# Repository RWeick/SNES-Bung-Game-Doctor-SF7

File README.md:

# SNES-Bung-Game-Doctor-SF7
The Kicad files and rom for the Bung Game Doctor SF7 for the SNES

This board has been tested and confirmed.
**30 Sep 2026: Thank you to CoolChecker for discovering that somehow a net failed to be connected - TC was not routed from the ASIC to the Floppy Controller. This has now been corrected.

Mainboard PCB Thickness: 1.6 mm
RAM PCB Thicknesses: 1.2 mm
SNES Attachment PCB Thickness: 1.2 mm

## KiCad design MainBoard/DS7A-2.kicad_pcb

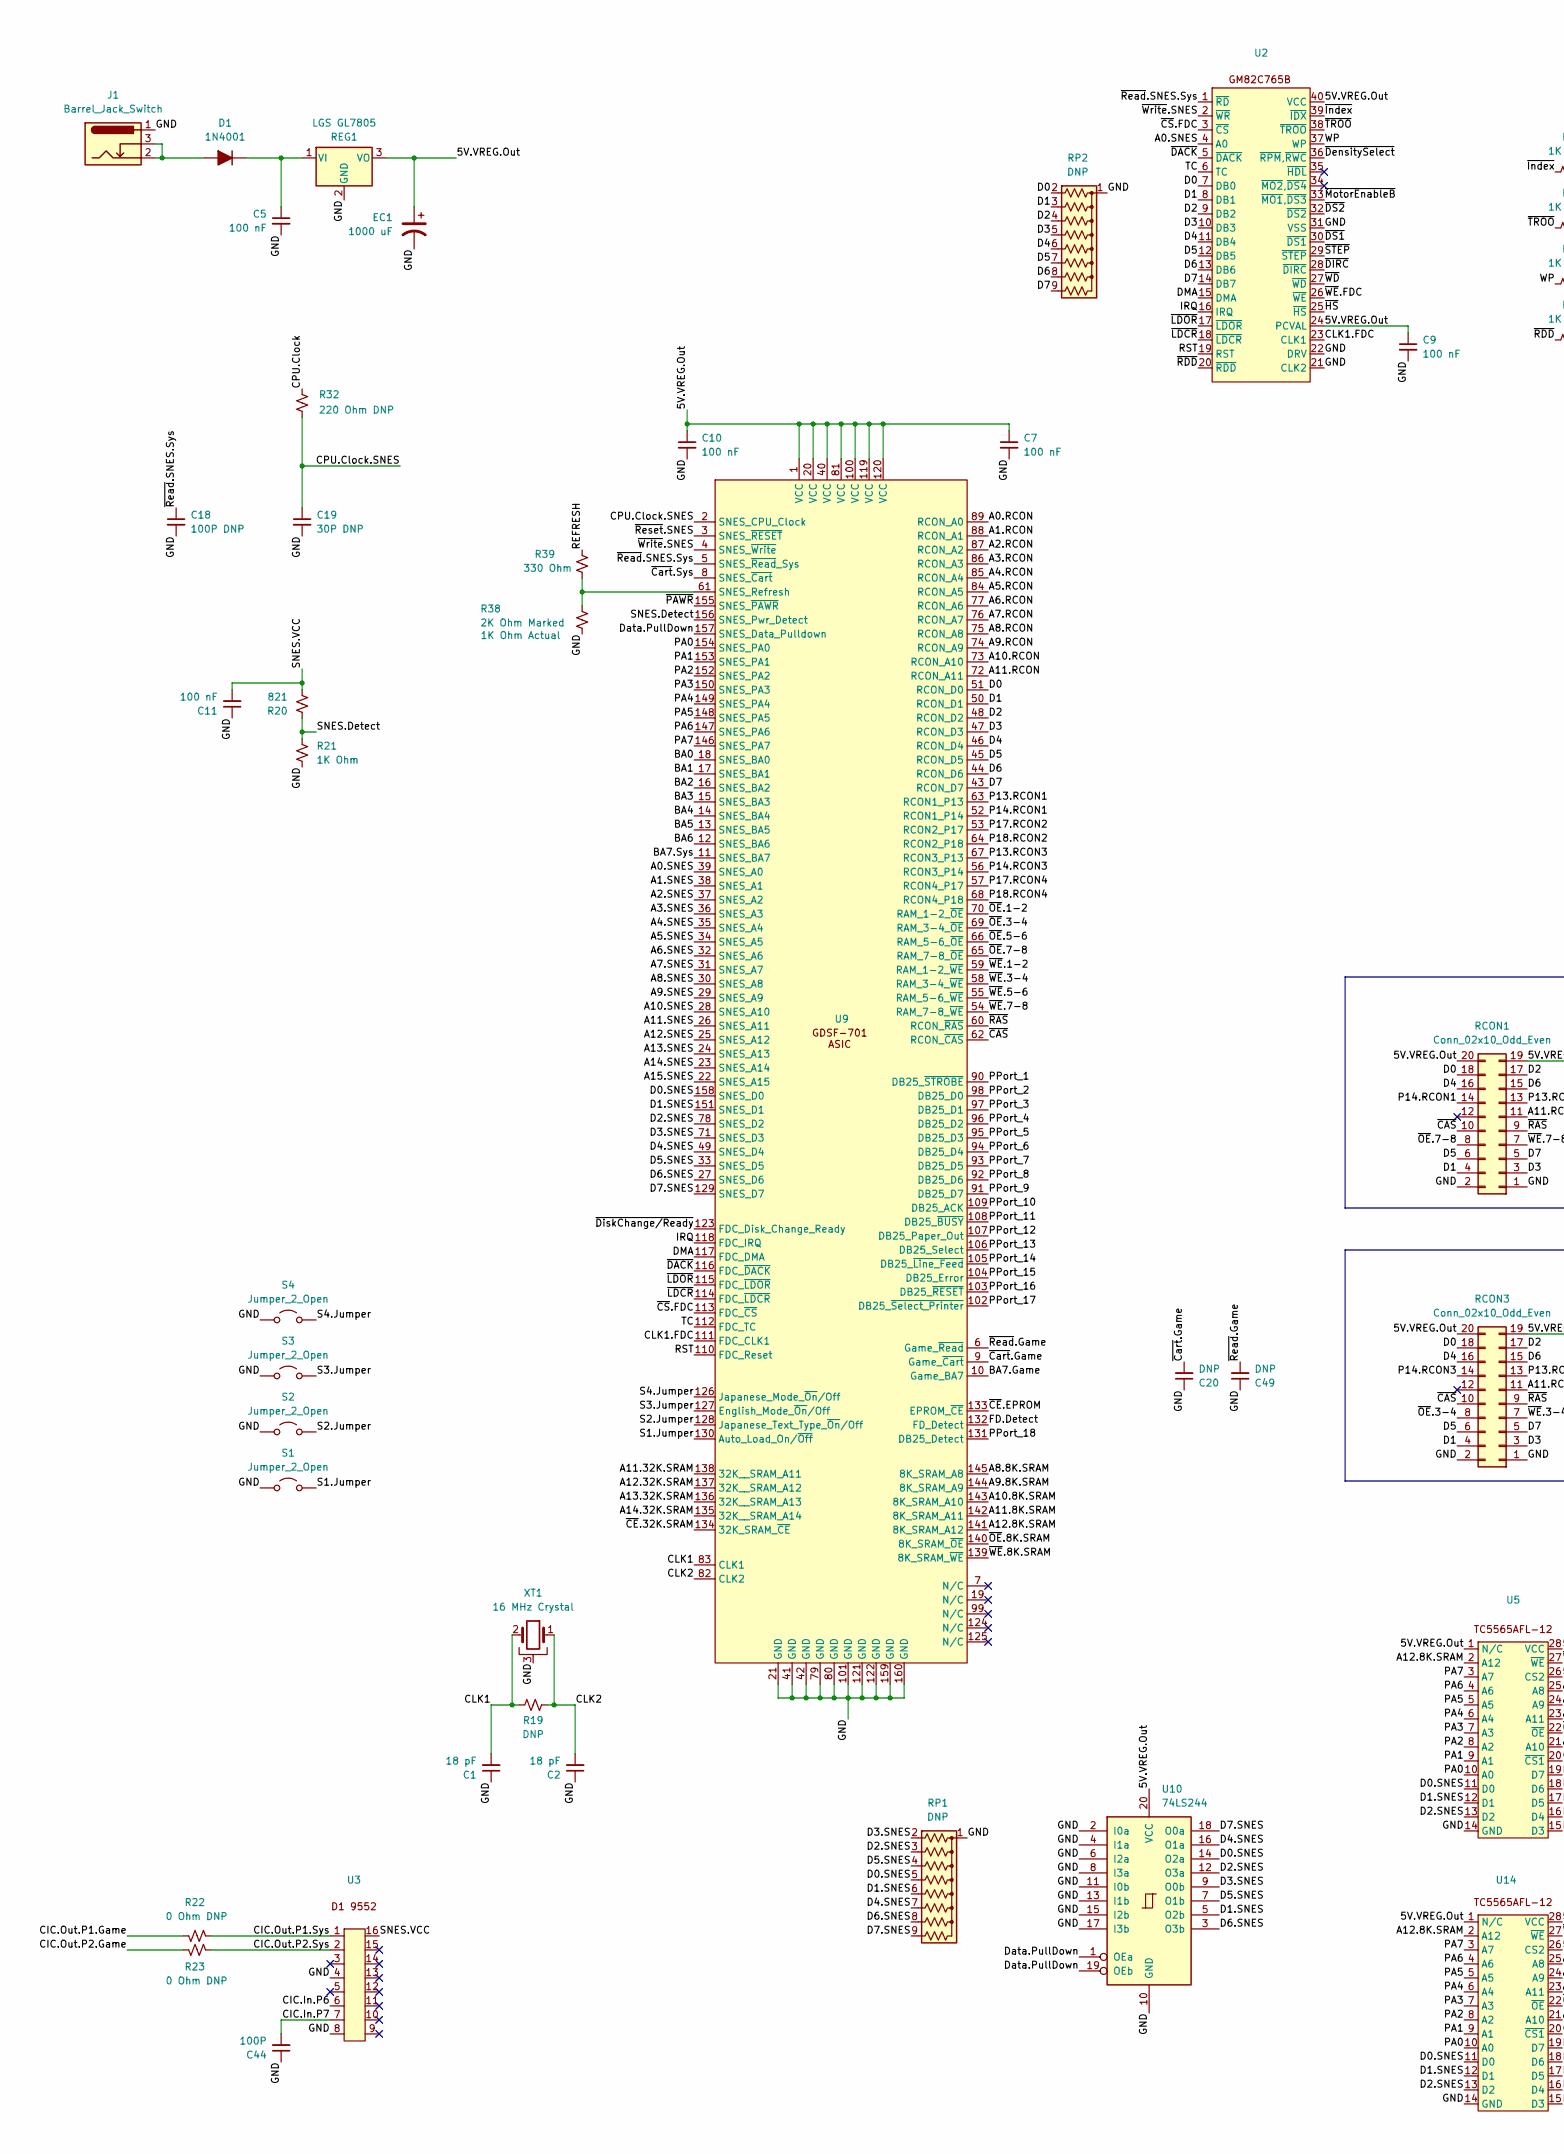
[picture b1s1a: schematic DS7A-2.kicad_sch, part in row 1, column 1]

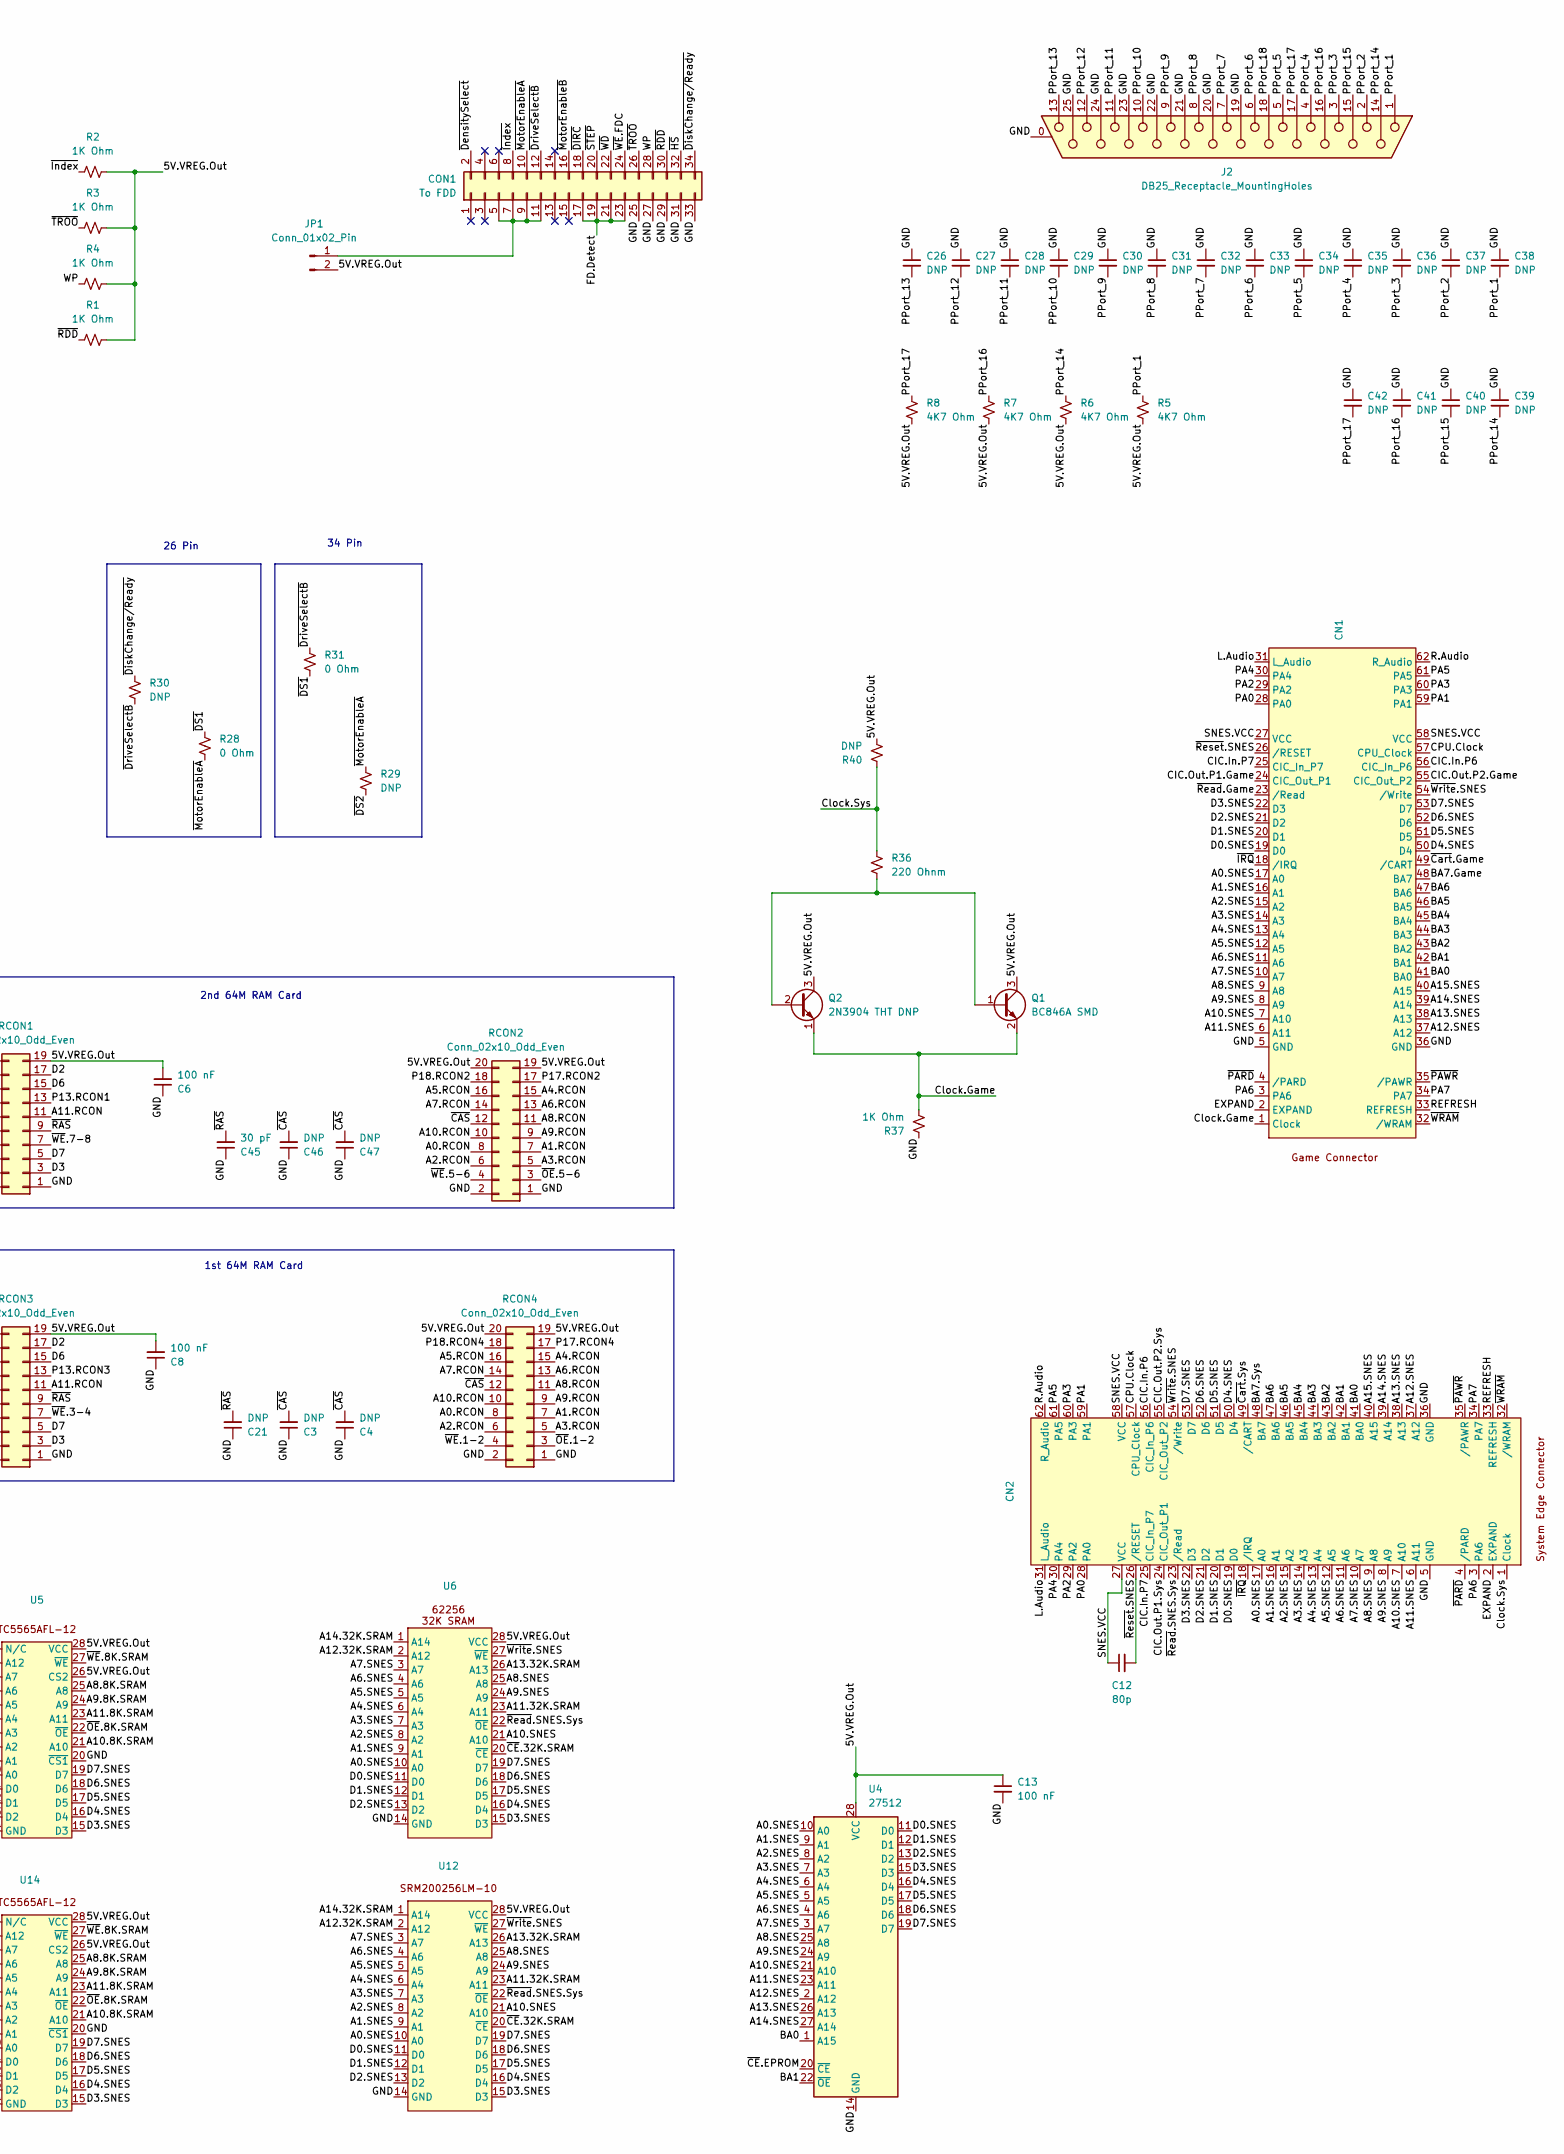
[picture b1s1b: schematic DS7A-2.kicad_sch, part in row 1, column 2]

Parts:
C1, C2: 18 pF; SMD Cap
C3, C4, C20, C21, C26, C27, C28, C29, C30, C31, C32, C33, C34, C35, C36, C37, C38, C39, C40, C41, C42, C46, C47, C49: DNP; SMD Cap
C5, C6, C7, C8, C9, C10, C11, C13: 100 nF; SMD Cap
C12: 80p; SMD Cap
C18: 100P DNP; SMD Cap
C19: 30P DNP; SMD Cap
C44: 100P; SMD Cap
C45: 30 pF; SMD Cap
CN1, CN2: Cartridge Slot
CON1: To FDD; PinSocket_2x17_P2.54mm_Vertical
D1: 1N4001; D_DO-41_SOD81_P10.16mm_Horizontal
EC1: 1000 uF; CP_Radial_D8.0mm_P3.50mm
J1: Barrel_Jack_Switch; DC Jack
J2: DB25_Receptacle_MountingHoles; DSUB-25_Female_Horizontal_P2.77x2.84mm_EdgePinOffset9.90mm_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
JP1: Conn_01x02_Pin; PinHeader_1x02_P2.54mm_Vertical
Q1: BC846A SMD; SOT-23
Q2: 2N3904 THT DNP; TO-92_Inline
R1, R2, R3, R4, R21, R37: 1K Ohm; SMD Resistor
R5, R6, R7, R8: 4K7 Ohm; SMD Resistor
R19, R29, R30, R40: DNP; SMD Resistor
R20: 821; SMD Resistor
R22, R23: 0 Ohm DNP; SMD Resistor
R28, R31: 0 Ohm; SMD Resistor
R32: 220 Ohm DNP; SMD Resistor
R36: 220 Ohnm; SMD Resistor
R38: 2K Ohm Marked; SMD Resistor
R39: 330 Ohm; SMD Resistor
RCON1, RCON2, RCON3, RCON4: Conn_02x10_Odd_Even; PinHeader_2x10_P2.54mm_Vertical
REG1: LGS GL7805; TO-220-3_Vertical
RP1, RP2: DNP; R_Array_SIP9
S1, S2, S3, S4: Jumper_2_Open; SolderJumper-2_P1.3mm_Open_RoundedPad1.0x1.5mm
U2: DIP-40_W15.24mm
U3: DIP-16_W7.62mm
U4: 27512; DIP-28_W15.24mm
U5, U6: DIP-28_W15.24mm
U9: GDSF-701
U10: 74LS244; DIP-20_W7.62mm
U12, U14: SOP-28_8.4x18.16mm_P1.27mm
XT1: 16 MHz Crystal; Crystal_AT310_D3.0mm_L10.0mm_Horizontal_1EP_style1

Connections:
/5V.VREG.Out: C6.2, C7.1, C8.2, C9.1, C10.1, C13.1, EC1.1, JP1.2, Q1.3 (C), Q2.3 (C), R1.2, R2.2, R3.2, R4.2, R5.2, R6.2, R7.2, R8.2, R40.2, RCON1.19, RCON1.20, RCON2.19, RCON2.20, RCON3.19, RCON3.20, RCON4.19, RCON4.20, REG1.3 (VO), U2.24 (PCVAL), U2.40 (VCC), U4.28 (VCC), U5.1 (N/C), U5.26 (CS2), U5.28 (VCC), U6.28 (VCC), U9.1 (VCC), U9.20 (VCC), U9.40 (VCC), U9.81 (VCC), U9.100 (VCC), U9.119 (VCC), U9.120 (VCC), U10.20 (VCC), U12.28 (VCC), U14.1 (N/C), U14.26 (CS2), U14.28 (VCC)
/A0.RCON: RCON2.8, RCON4.8, U9.89 (RCON_A0)
/A0.SNES: CN1.17 (A0), CN2.17 (A0), U2.4 (A0), U4.10 (A0), U6.10 (A0), U9.39 (SNES_A0), U12.10 (A0)
/A1.RCON: RCON2.7, RCON4.7, U9.88 (RCON_A1)
/A1.SNES: CN1.16 (A1), CN2.16 (A1), U4.9 (A1), U6.9 (A1), U9.38 (SNES_A1), U12.9 (A1)
/A2.RCON: RCON2.6, RCON4.6, U9.87 (RCON_A2)
/A2.SNES: CN1.15 (A2), CN2.15 (A2), U4.8 (A2), U6.8 (A2), U9.37 (SNES_A2), U12.8 (A2)
/A3.RCON: RCON2.5, RCON4.5, U9.86 (RCON_A3)
/A3.SNES: CN1.14 (A3), CN2.14 (A3), U4.7 (A3), U6.7 (A3), U9.36 (SNES_A3), U12.7 (A3)
/A4.RCON: RCON2.15, RCON4.15, U9.85 (RCON_A4)
/A4.SNES: CN1.13 (A4), CN2.13 (A4), U4.6 (A4), U6.6 (A4), U9.35 (SNES_A4), U12.6 (A4)
/A5.RCON: RCON2.16, RCON4.16, U9.84 (RCON_A5)
/A5.SNES: CN1.12 (A5), CN2.12 (A5), U4.5 (A5), U6.5 (A5), U9.34 (SNES_A5), U12.5 (A5)
/A6.RCON: RCON2.13, RCON4.13, U9.77 (RCON_A6)
/A6.SNES: CN1.11 (A6), CN2.11 (A6), U4.4 (A6), U6.4 (A6), U9.32 (SNES_A6), U12.4 (A6)
/A7.RCON: RCON2.14, RCON4.14, U9.76 (RCON_A7)
/A7.SNES: CN1.10 (A7), CN2.10 (A7), U4.3 (A7), U6.3 (A7), U9.31 (SNES_A7), U12.3 (A7)
/A8.8K.SRAM: U5.25 (A8), U9.145 (8K_SRAM_A8), U14.25 (A8)
/A8.RCON: RCON2.11, RCON4.11, U9.75 (RCON_A8)
/A8.SNES: CN1.9 (A8), CN2.9 (A8), U4.25 (A8), U6.25 (A8), U9.30 (SNES_A8), U12.25 (A8)
/A9.8K.SRAM: U5.24 (A9), U9.144 (8K_SRAM_A9), U14.24 (A9)
/A9.RCON: RCON2.9, RCON4.9, U9.74 (RCON_A9)
/A9.SNES: CN1.8 (A9), CN2.8 (A9), U4.24 (A9), U6.24 (A9), U9.29 (SNES_A9), U12.24 (A9)
/A10.8K.SRAM: U5.21 (A10), U9.143 (8K_SRAM_A10), U14.21 (A10)
/A10.RCON: RCON2.10, RCON4.10, U9.73 (RCON_A10)
/A10.SNES: CN1.7 (A10), CN2.7 (A10), U4.21 (A10), U6.21 (A10), U9.28 (SNES_A10), U12.21 (A10)
/A11.8K.SRAM: U5.23 (A11), U9.142 (8K_SRAM_A11), U14.23 (A11)
/A11.32K.SRAM: U6.23 (A11), U9.138 (32K__SRAM_A11), U12.23 (A11)
/A11.RCON: RCON1.11, RCON3.11, U9.72 (RCON_A11)
/A11.SNES: CN1.6 (A11), CN2.6 (A11), U4.23 (A11), U9.26 (SNES_A11)
/A12.8K.SRAM: U5.2 (A12), U9.141 (8K_SRAM_A12), U14.2 (A12)
/A12.32K.SRAM: U6.2 (A12), U9.137 (32K__SRAM_A12), U12.2 (A12)
/A12.SNES: CN1.37 (A12), CN2.37 (A12), U4.2 (A12), U9.25 (SNES_A12)
/A13.32K.SRAM: U6.26 (A13), U9.136 (32K__SRAM_A13), U12.26 (A13)
/A13.SNES: CN1.38 (A13), CN2.38 (A13), U4.26 (A13), U9.24 (SNES_A13)
/A14.32K.SRAM: U6.1 (A14), U9.135 (32K__SRAM_A14), U12.1 (A14)
/A14.SNES: CN1.39 (A14), CN2.39 (A14), U4.27 (A14), U9.23 (SNES_A14)
/A15.SNES: CN1.40 (A15), CN2.40 (A15), U9.22 (SNES_A15)
/BA0: CN1.41 (BA0), CN2.41 (BA0), U4.1 (A15), U9.18 (SNES_BA0)
/BA1: CN1.42 (BA1), CN2.42 (BA1), U4.22 (~OE), U9.17 (SNES_BA1)
/BA2: CN1.43 (BA2), CN2.43 (BA2), U9.16 (SNES_BA2)
/BA3: CN1.44 (BA3), CN2.44 (BA3), U9.15 (SNES_BA3)
/BA4: CN1.45 (BA4), CN2.45 (BA4), U9.14 (SNES_BA4)
/BA5: CN1.46 (BA5), CN2.46 (BA5), U9.13 (SNES_BA5)
/BA6: CN1.47 (BA6), CN2.47 (BA6), U9.12 (SNES_BA6)
/BA7.Game: CN1.48 (BA7), U9.10 (Game_BA7)
/BA7.Sys: CN2.48 (BA7), U9.11 (SNES_BA7)
/CIC.In.P6: CN1.56 (CIC_In_P6), CN2.56 (CIC_In_P6), U3.6
/CIC.In.P7: C44.2, CN1.25 (CIC_In_P7), CN2.25 (CIC_In_P7), U3.7
/CIC.Out.P1.Game: CN1.24 (CIC_Out_P1), R22.1
/CIC.Out.P1.Sys: CN2.24 (CIC_Out_P1), R22.2, U3.1
/CIC.Out.P2.Game: CN1.55 (CIC_Out_P2), R23.1
/CIC.Out.P2.Sys: CN2.55 (CIC_Out_P2), R23.2, U3.2
/CLK1: C1.2, R19.1, U9.83 (CLK1), XT1.2
/CLK1.FDC: U2.23 (CLK1), U9.111 (FDC_CLK1)
/CLK2: C2.2, R19.2, U9.82 (CLK2), XT1.1
/CPU.Clock: CN1.57 (CPU_Clock), CN2.57 (CPU_Clock), R32.2
/CPU.Clock.SNES: C19.1, R32.1, U9.2 (SNES_CPU_Clock)
/Clock.Game: CN1.1 (Clock), Q1.2 (E), Q2.1 (E), R37.2
/Clock.Sys: CN2.1 (Clock), R36.1, R40.1
/D0: RCON1.18, RCON3.18, RP2.2 (R1), U2.7 (DB0), U9.51 (RCON_D0)
/D0.SNES: CN1.19 (D0), CN2.19 (D0), RP1.5 (R4), U4.11 (D0), U5.11 (D0), U6.11 (D0), U9.158 (SNES_D0), U10.14 (O2a), U12.11 (D0), U14.11 (D0)
/D1: RCON1.4, RCON3.4, RP2.3 (R2), U2.8 (DB1), U9.50 (RCON_D1)
/D1.SNES: CN1.20 (D1), CN2.20 (D1), RP1.6 (R5), U4.12 (D1), U5.12 (D1), U6.12 (D1), U9.151 (SNES_D1), U10.5 (O2b), U12.12 (D1), U14.12 (D1)
/D2: RCON1.17, RCON3.17, RP2.4 (R3), U2.9 (DB2), U9.48 (RCON_D2)
/D2.SNES: CN1.21 (D2), CN2.21 (D2), RP1.3 (R2), U4.13 (D2), U5.13 (D2), U6.13 (D2), U9.78 (SNES_D2), U10.12 (O3a), U12.13 (D2), U14.13 (D2)
/D3: RCON1.3, RCON3.3, RP2.5 (R4), U2.10 (DB3), U9.47 (RCON_D3)
/D3.SNES: CN1.22 (D3), CN2.22 (D3), RP1.2 (R1), U4.15 (D3), U5.15 (D3), U6.15 (D3), U9.71 (SNES_D3), U10.9 (O0b), U12.15 (D3), U14.15 (D3)
/D4: RCON1.16, RCON3.16, RP2.6 (R5), U2.11 (DB4), U9.46 (RCON_D4)
/D4.SNES: CN1.50 (D4), CN2.50 (D4), RP1.7 (R6), U4.16 (D4), U5.16 (D4), U6.16 (D4), U9.49 (SNES_D4), U10.16 (O1a), U12.16 (D4), U14.16 (D4)
/D5: RCON1.6, RCON3.6, RP2.7 (R6), U2.12 (DB5), U9.45 (RCON_D5)
/D5.SNES: CN1.51 (D5), CN2.51 (D5), RP1.4 (R3), U4.17 (D5), U5.17 (D5), U6.17 (D5), U9.33 (SNES_D5), U10.7 (O1b), U12.17 (D5), U14.17 (D5)
/D6: RCON1.15, RCON3.15, RP2.8 (R7), U2.13 (DB6), U9.44 (RCON_D6)
/D6.SNES: CN1.52 (D6), CN2.52 (D6), RP1.8 (R7), U4.18 (D6), U5.18 (D6), U6.18 (D6), U9.27 (SNES_D6), U10.3 (O3b), U12.18 (D6), U14.18 (D6)
/D7: RCON1.5, RCON3.5, RP2.9 (R8), U2.14 (DB7), U9.43 (RCON_D7)
/D7.SNES: CN1.53 (D7), CN2.53 (D7), RP1.9 (R8), U4.19 (D7), U5.19 (D7), U6.19 (D7), U9.129 (SNES_D7), U10.18 (O0a), U12.19 (D7), U14.19 (D7)
/DMA: U2.15 (DMA), U9.117 (FDC_DMA)
/Data.PullDown: U9.157 (SNES_Data_Pulldown), U10.1 (OEa), U10.19 (OEb)
/EXPAND: CN1.2 (EXPAND), CN2.2 (EXPAND)
/FD.Detect: CON1.17, CON1.19, CON1.21, CON1.23, U9.132 (FD_Detect)
/GND: C1.1, C2.1, C3.1, C4.1, C5.2, C6.1, C7.2, C8.1, C9.2, C10.2, C11.1, C13.2, C18.2, C19.2, C20.1, C21.1, C26.1, C27.1, C28.1, C29.1, C30.1, C31.1, C32.1, C33.1, C34.1, C35.1, C36.1, C37.1, C38.1, C39.1, C40.1, C41.1, C42.1, C44.1, C45.1, C46.1, C47.1, C49.1, CN1.5 (GND), CN1.36 (GND), CN2.5 (GND), CN2.36 (GND), CON1.25, CON1.27, CON1.29, CON1.31, CON1.33, EC1.2, J1.1, J2.0 (PAD), J2.19, J2.20, J2.21, J2.22, J2.23, J2.24, J2.25, R21.2, R37.1, R38.1, RCON1.1, RCON1.2, RCON2.1, RCON2.2, RCON3.1, RCON3.2, RCON4.1, RCON4.2, REG1.2 (GND), RP1.1 (common), RP2.1 (common), S1.1 (A), S2.1 (A), S3.1 (A), S4.1 (A), U2.21 (CLK2), U2.22 (DRV), U2.31 (VSS), U3.4, U3.8, U4.14 (GND), U5.14 (GND), U5.20 (~CS1), U6.14 (GND), U9.21 (GND), U9.41 (GND), U9.42 (GND), U9.79 (GND), U9.80 (GND), U9.101 (GND), U9.121 (GND), U9.122 (GND), U9.159 (GND), U9.160 (GND), U10.2 (I0a), U10.4 (I1a), U10.6 (I2a), U10.8 (I3a), U10.10 (GND), U10.11 (I0b), U10.13 (I1b), U10.15 (I2b), U10.17 (I3b), U12.14 (GND), U14.14 (GND), U14.20 (~CS1), XT1.3
/IRQ: U2.16 (IRQ), U9.118 (FDC_IRQ)
/L.Audio: CN1.31 (L_Audio), CN2.31 (L_Audio)
/P13.RCON1: RCON1.13, U9.63 (RCON1_P13)
/P13.RCON3: RCON3.13, U9.67 (RCON3_P13)
/P14.RCON1: RCON1.14, U9.52 (RCON1_P14)
/P14.RCON3: RCON3.14, U9.56 (RCON3_P14)
/P17.RCON2: RCON2.17, U9.53 (RCON2_P17)
/P17.RCON4: RCON4.17, U9.57 (RCON4_P17)
/P18.RCON2: RCON2.18, U9.64 (RCON2_P18)
/P18.RCON4: RCON4.18, U9.68 (RCON4_P18)
/PA0: CN1.28 (PA0), CN2.28 (PA0), U5.10 (A0), U9.154 (SNES_PA0), U14.10 (A0)
/PA1: CN1.59 (PA1), CN2.59 (PA1), U5.9 (A1), U9.153 (SNES_PA1), U14.9 (A1)
/PA2: CN1.29 (PA2), CN2.29 (PA2), U5.8 (A2), U9.152 (SNES_PA2), U14.8 (A2)
/PA3: CN1.60 (PA3), CN2.60 (PA3), U5.7 (A3), U9.150 (SNES_PA3), U14.7 (A3)
/PA4: CN1.30 (PA4), CN2.30 (PA4), U5.6 (A4), U9.149 (SNES_PA4), U14.6 (A4)
/PA5: CN1.61 (PA5), CN2.61 (PA5), U5.5 (A5), U9.148 (SNES_PA5), U14.5 (A5)
/PA6: CN1.3 (PA6), CN2.3 (PA6), U5.4 (A6), U9.147 (SNES_PA6), U14.4 (A6)
/PA7: CN1.34 (PA7), CN2.34 (PA7), U5.3 (A7), U9.146 (SNES_PA7), U14.3 (A7)
/PPort_1: C38.2, J2.1, R5.1, U9.90 (DB25_~STROBE)
/PPort_2: C37.2, J2.2, U9.98 (DB25_D0)
/PPort_3: C36.2, J2.3, U9.97 (DB25_D1)
/PPort_4: C35.2, J2.4, U9.96 (DB25_D2)
/PPort_5: C34.2, J2.5, U9.95 (DB25_D3)
/PPort_6: C33.2, J2.6, U9.94 (DB25_D4)
/PPort_7: C32.2, J2.7, U9.93 (DB25_D5)
/PPort_8: C31.2, J2.8, U9.92 (DB25_D6)
/PPort_9: C30.2, J2.9, U9.91 (DB25_D7)
/PPort_10: C29.2, J2.10, U9.109 (DB25_ACK)
/PPort_11: C28.2, J2.11, U9.108 (DB25_~BUSY)
/PPort_12: C27.2, J2.12, U9.107 (DB25_Paper_Out)
/PPort_13: C26.2, J2.13, U9.106 (DB25_Select)
/PPort_14: C39.2, J2.14, R6.1, U9.105 (DB25_~Line_Feed)
/PPort_15: C40.2, J2.15, U9.104 (DB25_Error)
/PPort_16: C41.2, J2.16, R7.1, U9.103 (DB25_~RESET)
/PPort_17: C42.2, J2.17, R8.1, U9.102 (DB25_~Select_Printer)
/PPort_18: J2.18, U9.131 (DB25_Detect)
/R.Audio: CN1.62 (R_Audio), CN2.62 (R_Audio)
/REFRESH: CN1.33 (REFRESH), CN2.33 (REFRESH), R39.2
/RST: U2.19 (RST), U9.110 (FDC_Reset)
/S1.Jumper: S1.2 (B), U9.130 (Auto_Load_On/~Off)
/S2.Jumper: S2.2 (B), U9.128 (Japanese_Text_Type_~On/Off)
/S3.Jumper: S3.2 (B), U9.127 (English_Mode_~On/Off)
/S4.Jumper: S4.2 (B), U9.126 (Japanese_Mode_~On/Off)
/SNES.Detect: R20.1, R21.1, U9.156 (SNES_Pwr_Detect)
/SNES.VCC: C11.2, C12.1, CN1.27 (VCC), CN1.58 (VCC), CN2.27 (VCC), CN2.58 (VCC), R20.2, U3.16
/TC: U2.6 (TC), U9.112 (FDC_TC)
/WP: CON1.28, R4.1, U2.37 (WP)
/~CAS: C3.2, C4.2, C46.2, C47.2, RCON1.10, RCON2.12, RCON3.10, RCON4.12, U9.62 (RCON_~CAS)
/~CE.32K.SRAM: U6.20 (~CE), U9.134 (32K_SRAM_~CE), U12.20 (~CE)
/~CE.EPROM: U4.20 (~CE), U9.133 (EPROM_~CE)
/~CS.FDC: U2.3 (~CS), U9.113 (FDC_~CS)
/~Cart.Game: C20.2, CN1.49 (/CART), U9.9 (Game_~Cart)
/~Cart.Sys: CN2.49 (/CART), U9.8 (SNES_~Cart)
/~DACK: U2.5 (~DACK), U9.116 (FDC_~DACK)
/~DIRC: CON1.18, U2.28 (~DIRC)
/~DS1: R28.1, R31.2, U2.30 (~DS1)
/~DS2: R29.2, U2.32 (~DS2)
/~DensitySelect: CON1.2, U2.36 (~RPM,~RWC)
/~DiskChange/Ready: CON1.34, R30.1, U9.123 (FDC_Disk_Change_Ready)
/~DriveSelectB: CON1.12, R30.2, R31.1
/~HS: CON1.32, U2.25 (~HS)
/~IRQ: CN1.18 (/IRQ), CN2.18 (/IRQ)
/~Index: CON1.8, R2.1, U2.39 (~IDX)
/~LDCR: U2.18 (~LDCR), U9.114 (FDC_~LDCR)
/~LDOR: U2.17 (~LDOR), U9.115 (FDC_~LDOR)
/~MotorEnableA: CON1.10, R28.2, R29.1
/~MotorEnableB: CON1.16, U2.33 (~MO1,~DS3)
/~OE.1-2: RCON4.3, U9.70 (RAM_1-2_~OE)
/~OE.3-4: RCON3.8, U9.69 (RAM_3-4_~OE)
/~OE.5-6: RCON2.3, U9.66 (RAM_5-6_~OE)
/~OE.7-8: RCON1.8, U9.65 (RAM_7-8_~OE)
/~OE.8K.SRAM: U5.22 (~OE), U9.140 (8K_SRAM_~OE), U14.22 (~OE)
/~PARD: CN1.4 (/PARD), CN2.4 (/PARD)
/~PAWR: CN1.35 (/PAWR), CN2.35 (/PAWR), U9.155 (SNES_~PAWR)
/~RAS: C21.2, C45.2, RCON1.9, RCON3.9, U9.60 (RCON_~RAS)
/~RDD: CON1.30, R1.1, U2.20 (~RDD)
/~Read.Game: C49.2, CN1.23 (/Read), U9.6 (Game_~Read)
/~Read.SNES.Sys: C18.1, CN2.23 (/Read), U2.1 (~RD), U6.22 (~OE), U9.5 (SNES_~Read_Sys), U12.22 (~OE)
/~Reset.SNES: C12.2, CN1.26 (/RESET), CN2.26 (/RESET), U9.3 (SNES_~RESET)
/~STEP: CON1.20, U2.29 (~STEP)
/~TROO: CON1.26, R3.1, U2.38 (~TROO)
/~WD: CON1.22, U2.27 (~WD)
/~WE.1-2: RCON4.4, U9.59 (RAM_1-2_~WE)
/~WE.3-4: RCON3.7, U9.58 (RAM_3-4_~WE)
/~WE.5-6: RCON2.4, U9.55 (RAM_5-6_~WE)
/~WE.7-8: RCON1.7, U9.54 (RAM_7-8_~WE)
/~WE.8K.SRAM: U5.27 (~WE), U9.139 (8K_SRAM_~WE), U14.27 (~WE)
/~WE.FDC: CON1.24, U2.26 (~WE)
/~WRAM: CN1.32 (/WRAM), CN2.32 (/WRAM)
/~Write.SNES: CN1.54 (/Write), CN2.54 (/Write), U2.2 (~WR), U6.27 (~WE), U9.4 (SNES_~Write), U12.27 (~WE)
unnamed: CON1.5, CON1.7, CON1.9, CON1.11, JP1.1
unnamed: D1.2 (A), J1.2, J1.3
unnamed: C5.1, D1.1 (K), REG1.1 (VI)
unnamed: Q1.1 (B), Q2.2 (B), R36.2
unnamed: R38.2, R39.1, U9.61 (SNES_Refresh)

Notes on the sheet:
34 Pin
1st 64M RAM Card
2nd 64M RAM Card
26 Pin

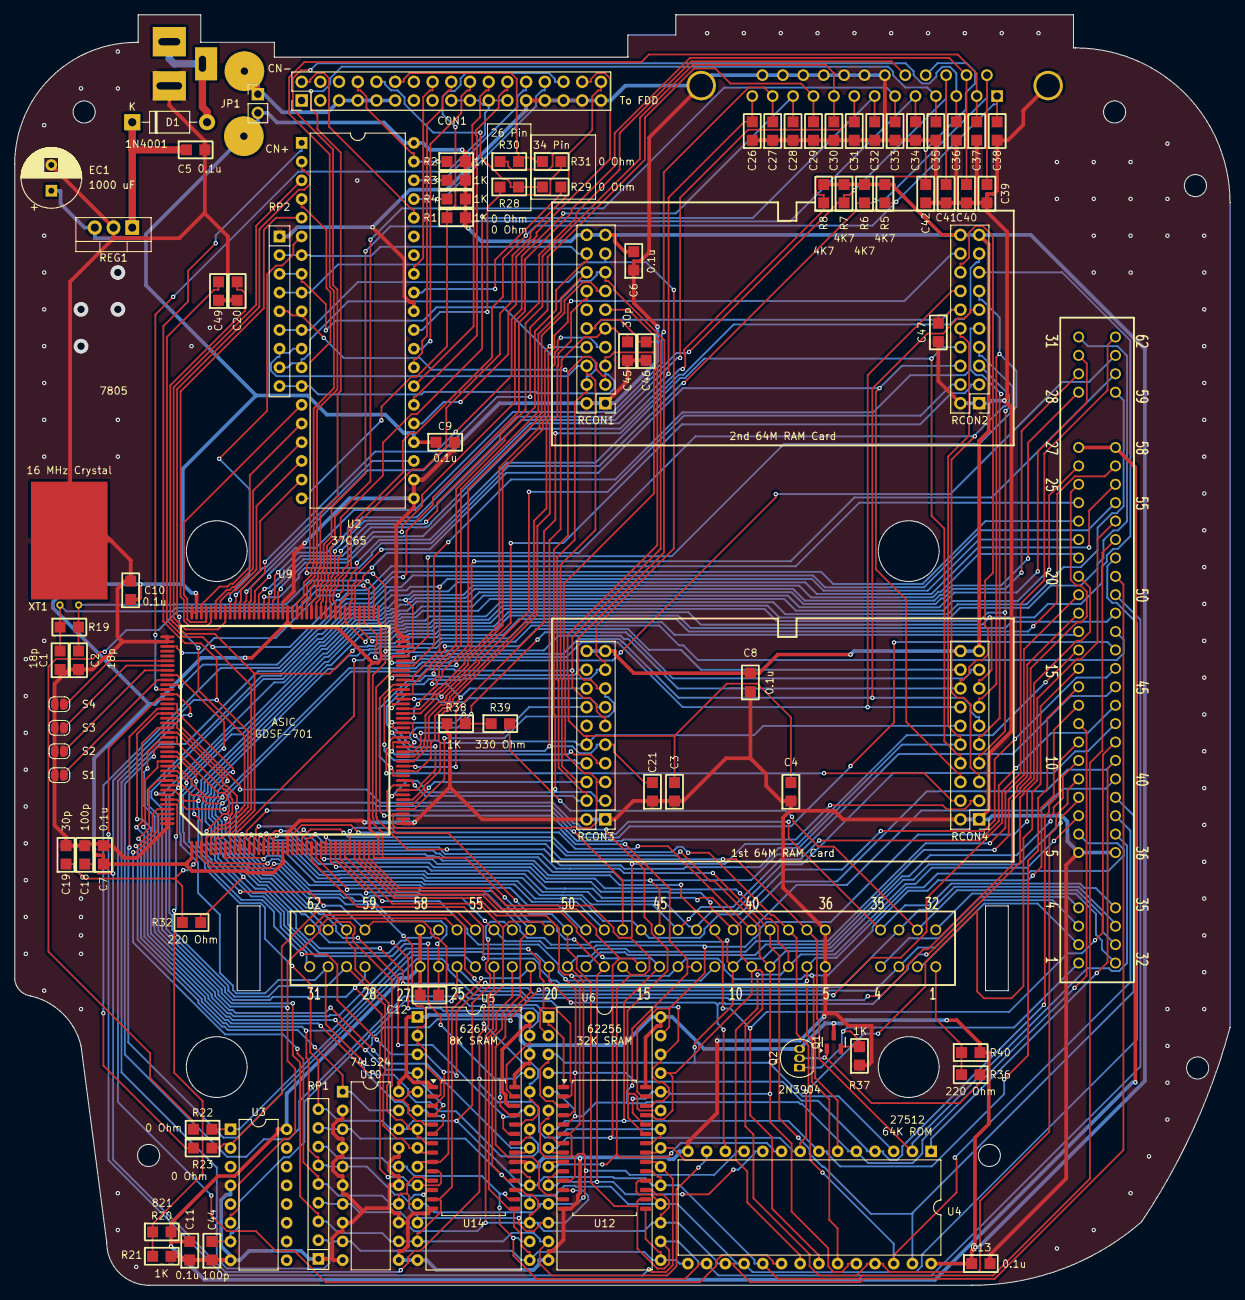
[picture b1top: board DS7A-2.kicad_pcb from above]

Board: 2 copper layers, 165.0 x 172.5 mm, 93 parts (1 on the bottom side), 176 nets.

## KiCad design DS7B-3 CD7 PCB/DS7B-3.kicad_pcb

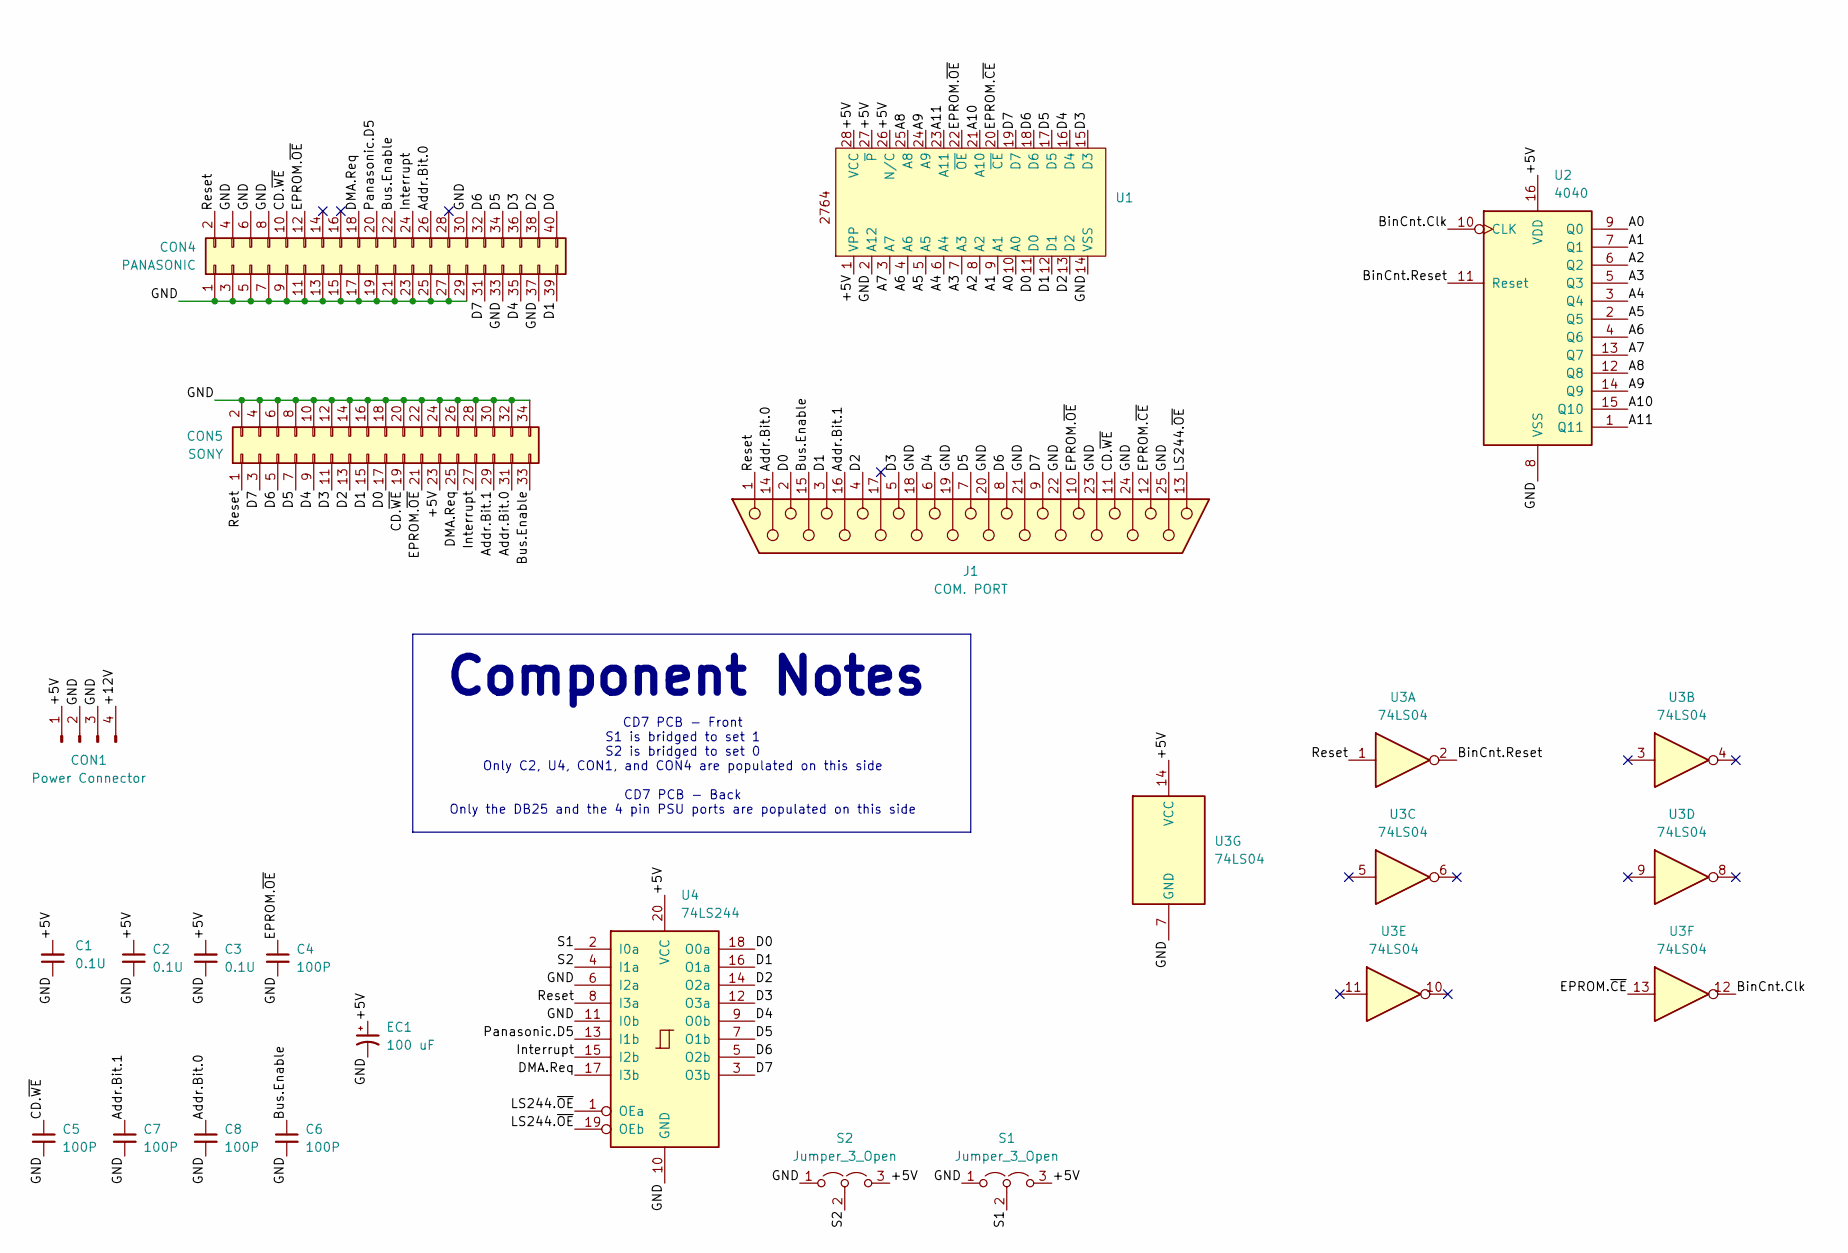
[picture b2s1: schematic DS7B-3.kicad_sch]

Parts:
C1, C2, C3: 0.1U; C_Disc_D5.0mm_W2.5mm_P5.00mm
C4, C5, C6, C7, C8: 100P; C_Disc_D3.8mm_W2.6mm_P2.50mm
CON1: Power Connector; Molex_KK-396_A-41791-0004_1x04_P3.96mm_Vertical
CON4: PANASONIC; IDC-Header_2x20_P2.54mm_Vertical
CON5: SONY; IDC-Header_2x17_P2.54mm_Vertical
EC1: 100 uF; CP_Radial_D8.0mm_P2.50mm
J1: COM. PORT; DSUB-25_Female_Vertical_P2.77x2.84mm_MountingHoles
S1, S2: Jumper_3_Open; PinHeader_1x03_P2.54mm_Vertical
U1: DIP-28_W15.24mm
U2: 4040; DIP-16_W7.62mm
U3: 74LS04; DIP-14_W7.62mm
U4: 74LS244; DIP-20_W7.62mm

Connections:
/+5V: C1.2, C2.1, C3.2, CON1.1, CON5.23, EC1.1, S1.3 (B), S2.3 (B), U1.1 (VPP), U1.26 (N/C), U1.27 (~P), U1.28 (VCC), U2.16 (VDD), U3.14 (VCC), U4.20 (VCC)
/+12V: CON1.4
/A0: U1.10 (A0), U2.9 (Q0)
/A1: U1.9 (A1), U2.7 (Q1)
/A2: U1.8 (A2), U2.6 (Q2)
/A3: U1.7 (A3), U2.5 (Q3)
/A4: U1.6 (A4), U2.3 (Q4)
/A5: U1.5 (A5), U2.2 (Q5)
/A6: U1.4 (A6), U2.4 (Q6)
/A7: U1.3 (A7), U2.13 (Q7)
/A8: U1.25 (A8), U2.12 (Q8)
/A9: U1.24 (A9), U2.14 (Q9)
/A10: U1.21 (A10), U2.15 (Q10)
/A11: U1.23 (A11), U2.1 (Q11)
/Addr.Bit.0: C8.1, CON4.26, CON5.31, J1.14
/Addr.Bit.1: C7.1, CON5.29, J1.16
/BinCnt.Clk: U2.10 (CLK), U3.12
/BinCnt.Reset: U2.11 (Reset), U3.2
/Bus.Enable: C6.1, CON4.22, CON5.33, J1.15
/CD.~WE: C5.1, CON4.10, CON5.19, J1.11
/D0: CON4.40, CON5.17, J1.2, U1.11 (D0), U4.18 (O0a)
/D1: CON4.39, CON5.15, J1.3, U1.12 (D1), U4.16 (O1a)
/D2: CON4.38, CON5.13, J1.4, U1.13 (D2), U4.14 (O2a)
/D3: CON4.36, CON5.11, J1.5, U1.15 (D3), U4.12 (O3a)
/D4: CON4.35, CON5.9, J1.6, U1.16 (D4), U4.9 (O0b)
/D5: CON4.34, CON5.7, J1.7, U1.17 (D5), U4.7 (O1b)
/D6: CON4.32, CON5.5, J1.8, U1.18 (D6), U4.5 (O2b)
/D7: CON4.31, CON5.3, J1.9, U1.19 (D7), U4.3 (O3b)
/DMA.Req: CON4.18, CON5.25, U4.17 (I3b)
/EPROM.~CE: J1.12, U1.20 (~CE), U3.13
/EPROM.~OE: C4.1, CON4.12, CON5.21, J1.10, U1.22 (~OE)
/GND: C1.1, C2.2, C3.1, C4.2, C5.2, C6.2, C7.2, C8.2, CON1.2, CON1.3, CON4.1, CON4.3, CON4.4, CON4.5, CON4.6, CON4.7, CON4.8, CON4.9, CON4.11, CON4.13, CON4.15, CON4.17, CON4.19, CON4.21, CON4.23, CON4.25, CON4.27, CON4.29, CON4.30, CON4.33, CON4.37, CON5.2, CON5.4, CON5.6, CON5.8, CON5.10, CON5.12, CON5.14, CON5.16, CON5.18, CON5.20, CON5.22, CON5.24, CON5.26, CON5.28, CON5.30, CON5.32, CON5.34, EC1.2, J1.18, J1.19, J1.20, J1.21, J1.22, J1.23, J1.24, J1.25, S1.1 (A), S2.1 (A), U1.2 (A12), U1.14 (VSS), U2.8 (VSS), U3.7 (GND), U4.6 (I2a), U4.10 (GND), U4.11 (I0b)
/Interrupt: CON4.24, CON5.27, U4.15 (I2b)
/LS244.~OE: J1.13, U4.1 (OEa), U4.19 (OEb)
/Panasonic.D5: CON4.20, U4.13 (I1b)
/Reset: CON4.2, CON5.1, J1.1, U3.1, U4.8 (I3a)
/S1: S1.2 (C), U4.2 (I0a)
/S2: S2.2 (C), U4.4 (I1a)

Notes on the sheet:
CD7 PCB - Front S1 is bridged to set 1 S2 is bridged to set 0 Only C2, U4, CON1, and CON4 are populated on this side CD7 PCB - Back Only the DB25 and the 4 pin PSU ports are populated on this side
Component Notes

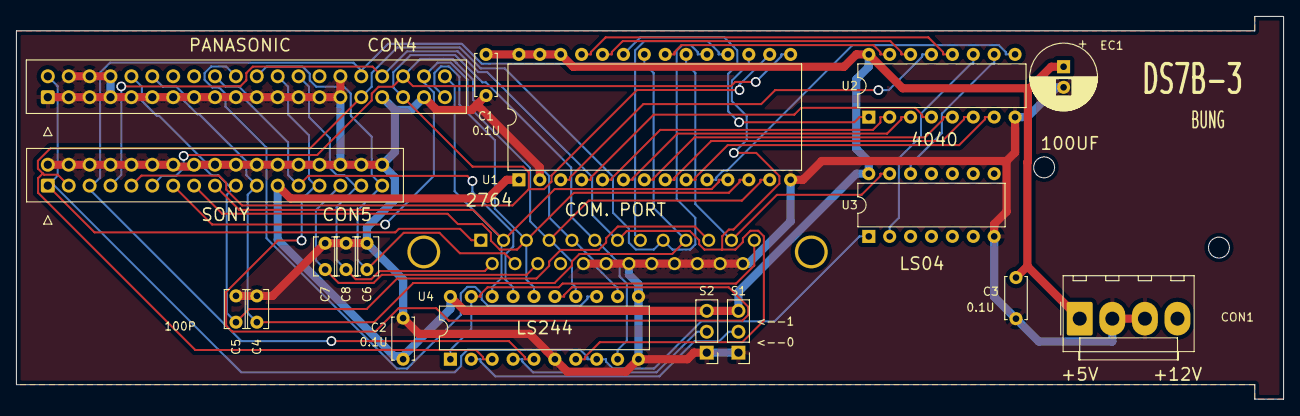
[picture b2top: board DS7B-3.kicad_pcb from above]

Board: 2 copper layers, 154.0 x 46.5 mm, 19 parts (1 on the bottom side), 37 nets.
